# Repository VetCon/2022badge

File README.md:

<div align="center">

  <h1> :skull: VETCON BADGE :skull: </h1>
  
  <p>
    TEAM 32 <span> · </span>2021-2022  
  </p>
  <p>
  SEMPER DISCO
  </p>

<!-- Badges -->
<p>

</p>

<h3>
  Quick Links!
</h3>
<h4>
    <a href="PLACEHOLDER">View Demo</a>
  <span> · </span>
    <a href="notes/README_Engineering.md">Quick Start Guide</a>
  <span> · </span>
    <a href="notes/README_HARDWARE.md">Hardware Guide</a>
  <span> · </span>
    <a href="notes/README_SOFTWARE.md">Software Guide</a>
</h4>

</div>

<br />

<!-- Table of Contents -->
# :notebook_with_decorative_cover: Table of Contents

- [:notebook_with_decorative_cover: Table of Contents](#notebook_with_decorative_cover-table-of-contents)
  - [:star2: About the Project](#star2-about-the-project)
    - [:label: Current Directory Structure](#label-current-directory-structure)
    - [:camera: Screenshots](#camera-screenshots)
    - [:space_invader: Tech Stack](#space_invader-tech-stack)
    - [:dart: Features](#dart-features)
      - [Embedded](#embedded)
      - [Minigames](#minigames)
  - [:toolbox: Getting Started](#toolbox-getting-started)
    - [:running: Quick(ly) Start!](#running-quickly-start)
  - [:eyes: Usage](#eyes-usage)
  - [:warning: License](#warning-license)
  - [:handshake: Contact](#handshake-contact)
  - [:gem: Acknowledgements](#gem-acknowledgements)

<!-- About the Project -->
## :star2: About the Project

### :label: Current Directory Structure
<a href="pcb/">pcb</a> – All PCB/eCAD files and schematics. Includes manufacturing .gbr files

<a href="enclosures/">enclosures</a> – All CAD files and schematics for the PCB enclosure. 

<a href="platformio/">platformio</a> – All code/firmware files concerning the MSP430 development board

<a href="notes/">notes</a> – Inital interview notes, MSP Documentation, useful infographics, additional READMEs

<a href="minigames/">minigames</a> – All code regarding Games 1, 2, and 3 (with CMake Files)

<a href="reports/">reports</a> – All previous reports for the 2021-2022 semester

<a href="derek/">derek</a> – Derek's personal folder for logbook maintenance

<a href="kircher/">kircher</a> – John's personal folder for logbook maintenance

<a href="etc/">etc</a> – Asset storage (logos, etc.)

<!-- Screenshots -->
### :camera: Screenshots

<div align="center"> 
  <p> PlatformIO VSCode Plugin "Home" Page </p>
  
</div>

<div align="center"> 
  <p> Sample Terminal Menu via Serial </p>
  
</div>

<div align="center"> 
  <p> Minigame #1 "Dino Run"</p>
  
</div>

<div align="center"> 
  <p> Minigame #2 "Coin Flip" </p>
  
</div>
<div align="center"> 
  <p> Minigame #3 "Text-based adventure" </p>
  
</div>

<!-- TechStack -->
### :space_invader: Tech Stack

<details>
  <summary>Embedded</summary>
  <ul>
    <li><a href="https://www.cplusplus.com/">C++</a></li>
    <li><a href="https://piolabs.com/company/about.html">PIOLabs</a></li>
    <li><a href="PlatformIO">PlatformIO</a></li>
    <li><a href="https://sourceforge.net/projects/mspgcc/">GCC Toolchain for MSP430 by TI</a></li>
    <li><a href="https://energia.nu/reference/">Energia Wiring-based Framework</a></li>
    <li><a href="https://registry.platformio.org/tools/platformio/tool-dslite">Uniflash Flash Tool for TI MCUs</a></li>
    <li><a href="http://wiring.org.co/">Wiring MCU Framework</a></li>
  </ul>
</details>

<details>
  <summary>Minigames</summary>
  <ul>
    <li><a href="https://phaser.io/">Phaser</a></li>
    <li><a href="https://webpack.js.org/">Webpack</a></li>
    <li><a href="https://www.typescriptlang.org/">Typescript</a></li>
    <li><a href="https://enable3d.io/">Enable3D</a></li>
    <li><a href="https://www.javascript.com/">Javascript</a></li>
    <li><a href="https://developer.mozilla.org/en-US/docs/Glossary/HTML5">HTML5</a></li>    
    <li><a href="https://cmake.org/">CMake</a></li>
  </ul>
</details>

<!-- Features -->
### :dart: Features

#### Embedded
- Interactive Shell/Terminal "UI"
- Customizeable
- Built-in LED Toggles
- Bluetooth Capable!
- Built-in low-power directives

#### Minigames
<details>
<summary> Game 1 </summary>
<ul>
<li> Interactive 'runner' game </li>
<li> Obfustication of source using Webpack and Babel for compilation</li>
<li> Hidden 'secrets' ;) </li>
</ul>
</details>
<details>
<summary> Game 2 </summary>
<ul>
<li> Interactive UI elements</li>
<li> Fluid animation using CSS! </li>
<li> Lightweight in-line JS </li>
<li> Built-in cookie storage and retrieval</li>
<li> Hidden 'secrets' ;) </li>
</ul>
</details>
<details>
<summary> Game 3</summary>
<ul>
<li> Interactive decision-based RPG-like text adventure </li>
<li> Open-ended Game Engine with Global Update features for future development and hackability </li>
<li> Text Engine incorporated at Compile-Time with simple .tsv formatting </li>
<li> Built-in undetectable "malware" with std::Threads </li>
<li> Hidden 'secrets' ;) </li>
</ul>
</details>

<!-- Getting Started -->
## 	:toolbox: Getting Started

<!-- Run Locally -->
### :running: Quick(ly) Start!

Clone the project

```bash
  git clone https://github.com/derekbarbosa/EC463.git
```

Then refer to the Quick Start Guide in its entirety! :)
[Quick Start Guide](notes/README_Engineering.md)

<!-- Usage -->
## :eyes: Usage

For a more detailed breakdown of the software components, how they work, how to implement them and how to expand on them, please refer to the [Software Guide](./notes/README_SOFTWARE.md)

For notes and explanation regarding hardware, building a functional breadboard prototype, understanding the modularity of several components, and PCB breakdown, please refer to the [Hardware Guide](./notes/README_HARDWARE.md)

<!-- License -->
## :warning: License

Distributed under the GNU GPL v3 LICENSE. See  <a href="https://www.github.com/derekbarbosa/EC463/blob/main/LICENSE">LICENSE.TXT</a> for more information.

<!-- Contact -->
## :handshake: Contact

<h4>Client</h4>

Mike Jones - jonesmlr (AT) gmail (dot) com

<h4> Team Members </h4>

<br> Derek Barbosa - dbarbosa (AT) bu (dot) edu </br>
<br> Ryan Sullivan - ryanbs (AT) bu (dot) edu </br>
<br> John Kircher - kircherj (AT) bu (dot) edu </br>
<br> Julian Padgett - jpadgett (AT) bu (dot) edu </br>
<br> Carlos Ortiz - cartex10 (AT) bu (dot) edu </br>

<br> Project Link: [https://github.com/derekbarbosa/EC463](https://github.com/derekbarbosa/EC463) </br>

<!-- Acknowledgments -->
## :gem: Acknowledgements

Some shout-outs, acknowledgements and resources!

 - [Shields.io](https://shields.io/)
 - [Awesome README](https://github.com/matiassingers/awesome-readme)
 - [Emoji Cheat Sheet](https://github.com/ikatyang/emoji-cheat-sheet/blob/master/README.md#travel--places)
 - [Make your own Dino Chrome Game!](https://www.youtube.com/watch?v=VOtZ6yNqH84)
 - [Using a 16x2 LCD with Arduino](https://www.makerguides.com/character-lcd-arduino-tutorial/)
 - [Making a Coin Toss Game](https://www.foolishdeveloper.com/2021/10/coin-flip-game-using-javascript.html)

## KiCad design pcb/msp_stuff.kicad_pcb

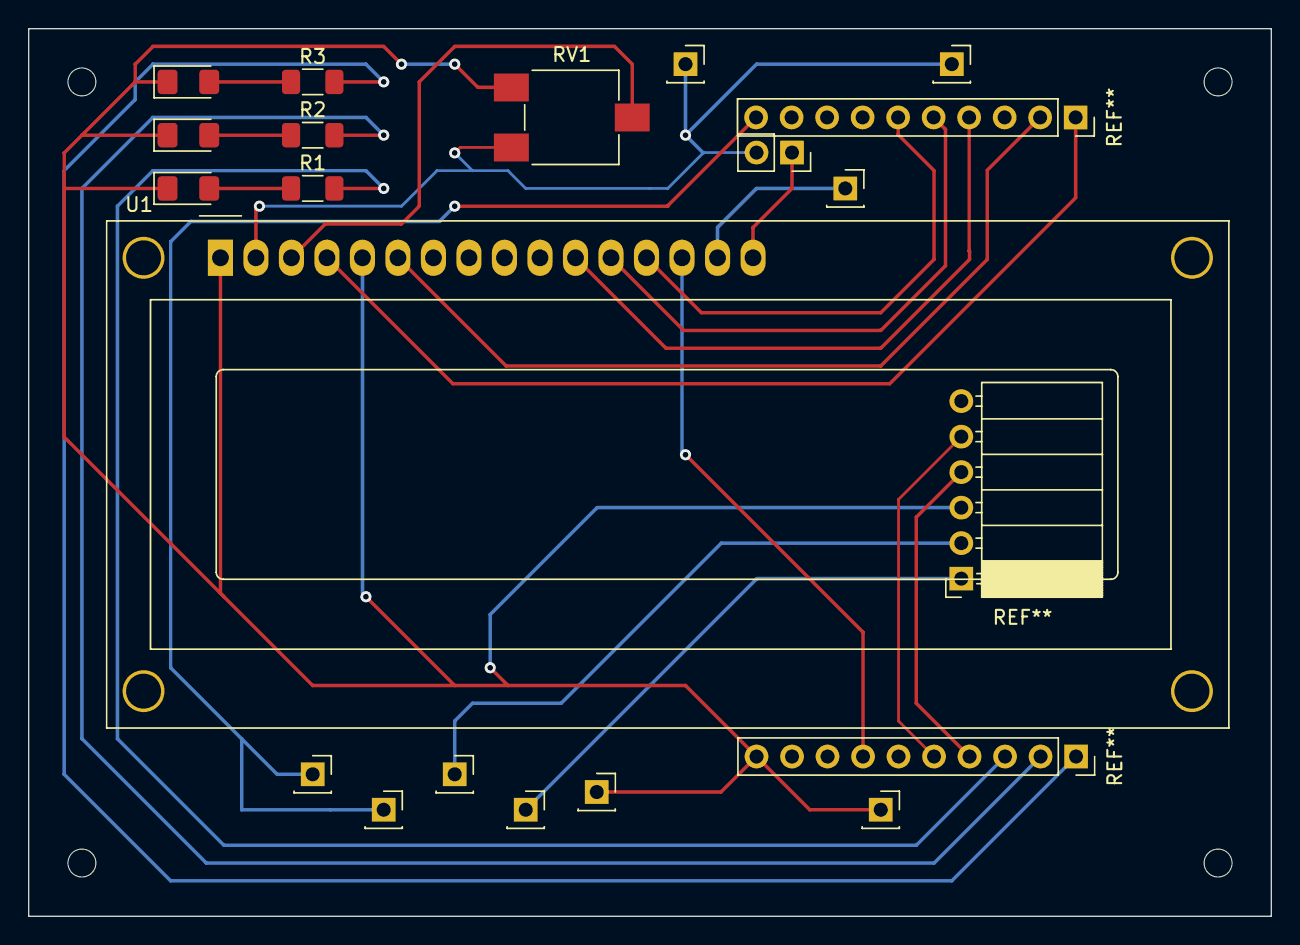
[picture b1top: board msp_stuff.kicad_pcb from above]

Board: 2 copper layers, 88.9 x 63.5 mm, 8 parts (0 on the bottom side), 5 nets.

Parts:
D1, D2, D3: LED; LED_1206_3216Metric_Pad1.42x1.75mm_HandSolder
R1, R2, R3: R_Small_US; R_1206_3216Metric_Pad1.30x1.75mm_HandSolder
RV1: R_Potentiometer; Potentiometer_ACP_CA6-VSMD_Vertical
U1: RC1602A-GHW-ESX; WC1602A

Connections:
GND: D1.1 (K), D2.1 (K), D3.1 (K), RV1.3, U1.1 (VSS), U1.5 (R/~W), U1.16 (K)
unnamed: D1.2 (A), R1.1
unnamed: D2.2 (A), R2.1
unnamed: D3.2 (A), R3.1
unnamed: RV1.2, U1.3 (Vo)

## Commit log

2021-02-14 Create Ribbon Ideas
2021-04-10 Add files via upload
    You can add supports for the button holes, may not need it..
    Infill up to you. more infill better the sides of the case.
2022-08-28 initial push of 2022
2022-08-28 remove some extra stuffs
